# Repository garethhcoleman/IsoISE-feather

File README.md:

# IsoISE-feather
##Hardware files for IsoISE feather board

In this repo you will find all the design files; I hope it is everything you need to reproduce and hopefully improve my work.

This circuit is heavily based on wonderful work by Ryan Edwards at sparkyswidgets.com.

I emailed Ryan because I wanted to ask if he was happy for me to just make his isoion project, which is not strictly necessary but I think is good manners. He gave me his blessing to go ahead. I thought it was especially important to do this since he was selling his projects (although not this one, my orignal motivation for making it) and I wasn't then intending to modify his design. Subsequently I took the bull by the horns and dove into (partially!) understanding and modifying his designs, so I took his more advanced [ion selective electrode interface project](https://www.sparkyswidgets.com/portfolio-item/ion-selective-electrode-interface/) and went from there.

As you can see by comparing our circuits, I copied his design for the isolated I2C based ADC and digital pot, applied to a TL072 JFET op-amp front end. The only significant changes I made were to replace the isolated power supply and separate -5V generator with an isolated supply able to generate +-5V from 3.3V. I did this because the original ADUM6010 datasheet does not recommend the combination of VIN=3.3V and VOUT=5V.

The PCB layout is my own work, my first ever board produced and already I can see issues!! The guard rings around the signal input pin are very tightly spaced making soldering difficult - in a future revision I will increase the spacing there. I somehow ended up skipping the reference R3 - so there are 11 resistors on board numbered R1-R12. Again, I'll correct this in future revisions. I didn't pay much attention to silkscreen component references so assembly will require reference to the board layout in Kicad....

I'm following Dave Jones' OSHW logo and definition: https://www.eevblog.com/oshw/

S = Schematic - Included
P = PCB - Included
F = Firmware and/or software - TO BE DONE
M = Mechanical CAD files - NOT APPLICABLE
D = Design Documentation - This document
B = Bill Of Materials - Included
C = License used allows for commercial use - YES

I've used open software to produce these files: Kicad 4.0.7, LibreOffice 4.3 and Remarkable 1.87

You can order the revision 1 board at [OSH Park](https://oshpark.com/shared_projects/bHu0gW7W).
Additionally, a shared basket of almost all the required components is [available at digikey](http://www.digikey.co.uk/short/jpfbn8).

Licensed under the Creative Commons Attribution-ShareAlike 3.0 Unported license, following the license of the originating project.

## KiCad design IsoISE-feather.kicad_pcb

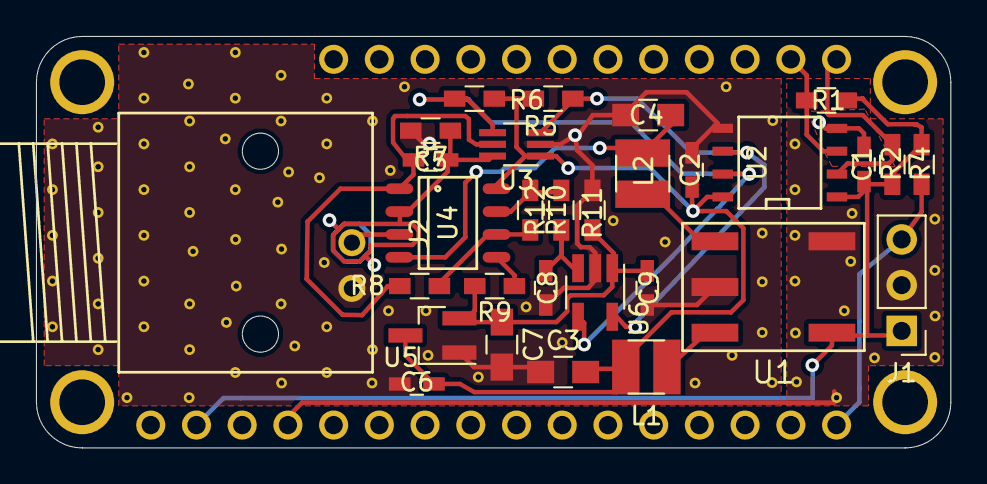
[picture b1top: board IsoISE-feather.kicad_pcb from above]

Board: 2 copper layers, 50.8 x 22.9 mm, 31 parts (0 on the bottom side), 20 nets.

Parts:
C1, C2, C5, C6, C9: 0.1uF; C_0603_HandSoldering
C3, C4, C7: 10uF; C_0805_HandSoldering
C8: 220pF; C_0603_HandSoldering
J1: Conn_01x03; Pin_Header_Straight_1x03_Pitch2.54mm
J2: BNC; BNC_Socket_Gmod
J3: FEATHER; FeatherWing
L1, L2: 10uH; Inductor_Murata_8200
R1, R2, R9: 3K; R_0603_HandSoldering
R4, R5, R6: 4.7K; R_0603_HandSoldering
R7: 10K; R_0603_HandSoldering
R8, R10: 100K; R_0603_HandSoldering
R11: 1K; R_0603_HandSoldering
R12: 500R; R_0603_HandSoldering
U1: MTU1D0305MC; 5pinMTU
U2: ADUM1250ARZ; SOIC-8-N
U3: MCP4017; SOT-363_SC-70-6_Handsoldering
U4: TL072; SOP-8L
U5: REF3130; SOT-23_Handsoldering
U6: MCP3221; SOT-23-5_HandSoldering

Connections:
/21: J1.3, J3.16, R4.2
/SCL: J3.27, R1.2, U2.3
/SDA: J3.28, R2.2, U2.2
Earth: C2.1, C3.1, C4.2, C6.2, C7.2, C8.1, C9.1, J2.2, R7.2, R11.1, U1.5, U2.5, U3.2, U5.1, U6.2
GND: C1.1, J1.2, J3.4, U1.3, U2.4
unnamed: C5.1, R8.2, U3.5, U4.1
unnamed: C5.2, R7.1, U3.6, U4.2
unnamed: C7.1, C9.2, R9.2, R11.2, U5.2, U6.1
unnamed: C8.2, R12.1, U6.3
unnamed: J2.1, U4.3
unnamed: L1.1, U1.6
unnamed: L2.1, U1.4
unnamed: R5.2, U2.6, U3.3, U6.5
unnamed: R6.2, U2.7, U3.4, U6.4
unnamed: R9.1, U4.5
unnamed: R10.1, R12.2, U4.7
unnamed: R8.1, R10.2, U4.6
VCC: C1.2, J1.1, J3.2, R1.1, R2.1, R4.1, U1.1, U2.1
VDD: C2.2, C3.2, C6.1, L1.2, R5.1, R6.1, U2.8, U3.1, U4.8, U5.3
VEE: C4.1, L2.2, U4.4

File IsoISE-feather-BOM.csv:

Ref,Value,Part Ordered,Footprint,Datasheet
U1,MTU1D0305MC,MTU1D0305MC,5pinMTU,https://power.murata.com/data/power/ncl/kdc_mtu1.pdf
U2,ADUM1250,ADUM1250ARZ,SOIC-8-N,http://www.analog.com/media/en/technical-documentation/data-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
U3,MCP4017,MCP4017T-104E/LT,SOT-363_SC-70-6,http://ww1.microchip.com/downloads/en/DeviceDoc/22147a.pdf
U4,TL072,TL072BIDT,SOP-8L,http://www.st.com/content/ccc/resource/technical/document/da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
U5,REF3130,REF3130AIDBZT,SOT-23-3,http://www.ti.com/lit/ds/symlink/ref3130.pdf
U6,MCP3221,MCP3221A5T-I/OT,SOT-23-5,http://ww1.microchip.com/downloads/en/DeviceDoc/20001732E.pdf
C1,0.1uF,C0603C104K9RAC7867,603,https://content.kemet.com/datasheets/KEM_C1002_X7R_SMD.pdf
C2,0.1uF,C0603C104K9RAC7867,603,https://content.kemet.com/datasheets/KEM_C1002_X7R_SMD.pdf
C3,10uF,C0805C106M9PACTU,805,https://content.kemet.com/datasheets/KEM_C1002_X7R_SMD.pdf
C4,10uF,C0805C106M9PACTU,805,https://content.kemet.com/datasheets/KEM_C1002_X7R_SMD.pdf
C5,0.1uF,C0603C104K9RAC7867,603,https://content.kemet.com/datasheets/KEM_C1002_X7R_SMD.pdf
C6,0.1uF,C0603C104K9RAC7867,603,https://content.kemet.com/datasheets/KEM_C1002_X7R_SMD.pdf
C7,10uF,C0805C106M9PACTU,805,https://content.kemet.com/datasheets/KEM_C1002_X7R_SMD.pdf
C8,220pF,C0603C221K8RAC7867,603,https://content.kemet.com/datasheets/KEM_C1002_X7R_SMD.pdf
C9,0.1uF,C0603C104K9RAC7867,603,https://content.kemet.com/datasheets/KEM_C1002_X7R_SMD.pdf
J1,Conn_01x03,Standard pin header,1x03_Pitch2.54mm,
J2,BNC,31-5431,BNC-Amphenol,https://www.amphenolrf.com/downloads/dl/file/id/7797/product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
J3,FeatherWing,OshPARK,,
L1,10uH,82103C,Murata_8200,https://www.murata-ps.com/data/magnetics/kmp_8200c.pdf
L2,10uH,82103C,Murata_8200,https://www.murata-ps.com/data/magnetics/kmp_8200c.pdf
R1,3K,CRCW06033K00FKEAC,603,
R2,3K,CRCW06033K00FKEAC,603,
R4,4.7K,RCA06034K70FKEA,603,
R5,4.7K,RCA06034K70FKEA,603,
R6,4.7K,RCA06034K70FKEA,603,
R7,10K,RT0603DRD0710KL,603,
R8,100K,AT0603DRD07100KL,603,
R9,3K,CRCW06033K00FKEAC,603,
R10,100K,AT0603DRD07100KL,603,
R11,1K,RT0603DRD071KL,603,
R12,500R,RT0603DRD07499RL,603,

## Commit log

2018-03-23 added first draft of kicad files
2018-03-23 tweaked silkscreen and replaced bnc to get 3d model..
2018-03-23 added project file and pdf of schematic for non-kicad users
2018-04-03 files as submitted to oshpark
2018-04-03 added seperate BOM as .csv
2018-04-03 added real part numbers to BOM and digikey basket
2018-04-03 Added photo and completed README.md
2018-04-04 corrected details in README
2018-04-09 updated logo on board
2018-04-10 began design of rev2 - added theory of operation document
